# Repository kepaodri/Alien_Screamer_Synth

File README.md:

# Alien_Screamer_Synth
PCB design for "Alien Screamer" (modified) synthesizer (original design by Ray Wilson) in 4-layer stackup using THT components.

## 👽👾 Project Description
The **Alien Screamer** Analog Noise Box is a classic Lo-Fi analog synthesizer designed by Ray Wilson of *Music From Outer Space* capable to creating Sci-Fi sound effects. It serves as an excellent introductory project for synth-DIY enthusiasts, providing a hands-on way to learn about oscillators, modulation, and integrated circuit amplification.

For more detailed technical information and the original schematics, visit the [MFOS Alien Screamer Noise Box](https://musicfromouterspace.com/analogsynth_new/ALIENSCREAMER/ALIENSCREAMER.php)

## 🚀 Main Features
* **Wide-Range VCO:** A ramp-core oscillator driven by an exponential V-to-I converter, capable of frequencies from sub-audio clicks to 10kHz.
* **Integrated LFO:** A square-wave oscillator with adjustable rate and depth.
* **Waveform Shaping:** Toggle between square, low-pass filtered, and differentiated "tweet" waveforms for diverse modulation.
* **Sync Effects:** Hard-sync capability where the LFO resets the VCO for aggressive, complex timbres.
* **Built-in Audio:** Includes an LM386-based 1W amplifier and 8-Ohm speaker for portability.
* **9V-Battery Powered:** Optimized for low current draw (~10mA) on a single 9V battery.

## 🛠 Technical Overview
The circuit is built around 2x primary ICs:
- LM324 (Quad Op-Amp): Handles the VCO exponential converter, the ramp generator/comparator, and the LFO
- LM386 (Power Amp): Drives the internal speaker
- 4x Control Potentiometers: LFO Frequency + LFO Modulation Depth + VCO Frecuency + Volume 
- 2x Control Switches: LFO Modulation Waveform Selector + Synchro Effect

## 📂 Project Structure
* `doc/` - KiCad schematic and Datasheets.
* `bom/` - Bill of Materials (BOM) for component sourcing.
* `hardware/` - KiCad Design files (schematic and PCB layout routing).
* `gerbers/` - PCB gerber and drill files for production.
* `renders/` - High quality PCB images.

### PCB Features
- Layers: 4
- Thickness: 1.6mm
- Width: 250mm
- Heigth: 119.5mm

### 3D Render

## Tools Used
KiCad: 9.0.4

> **Note:** This project is designed for educational and DIY purposes. Original design by Ray Wilson (Music From Outer Space).

## Disclaimer
\*\*This design is provided "AS-IS" without any express or implied warranties.\*\* The author is not responsible for any damage to equipment, fire, or personal injury resulting from the assembly or use of this PCB.

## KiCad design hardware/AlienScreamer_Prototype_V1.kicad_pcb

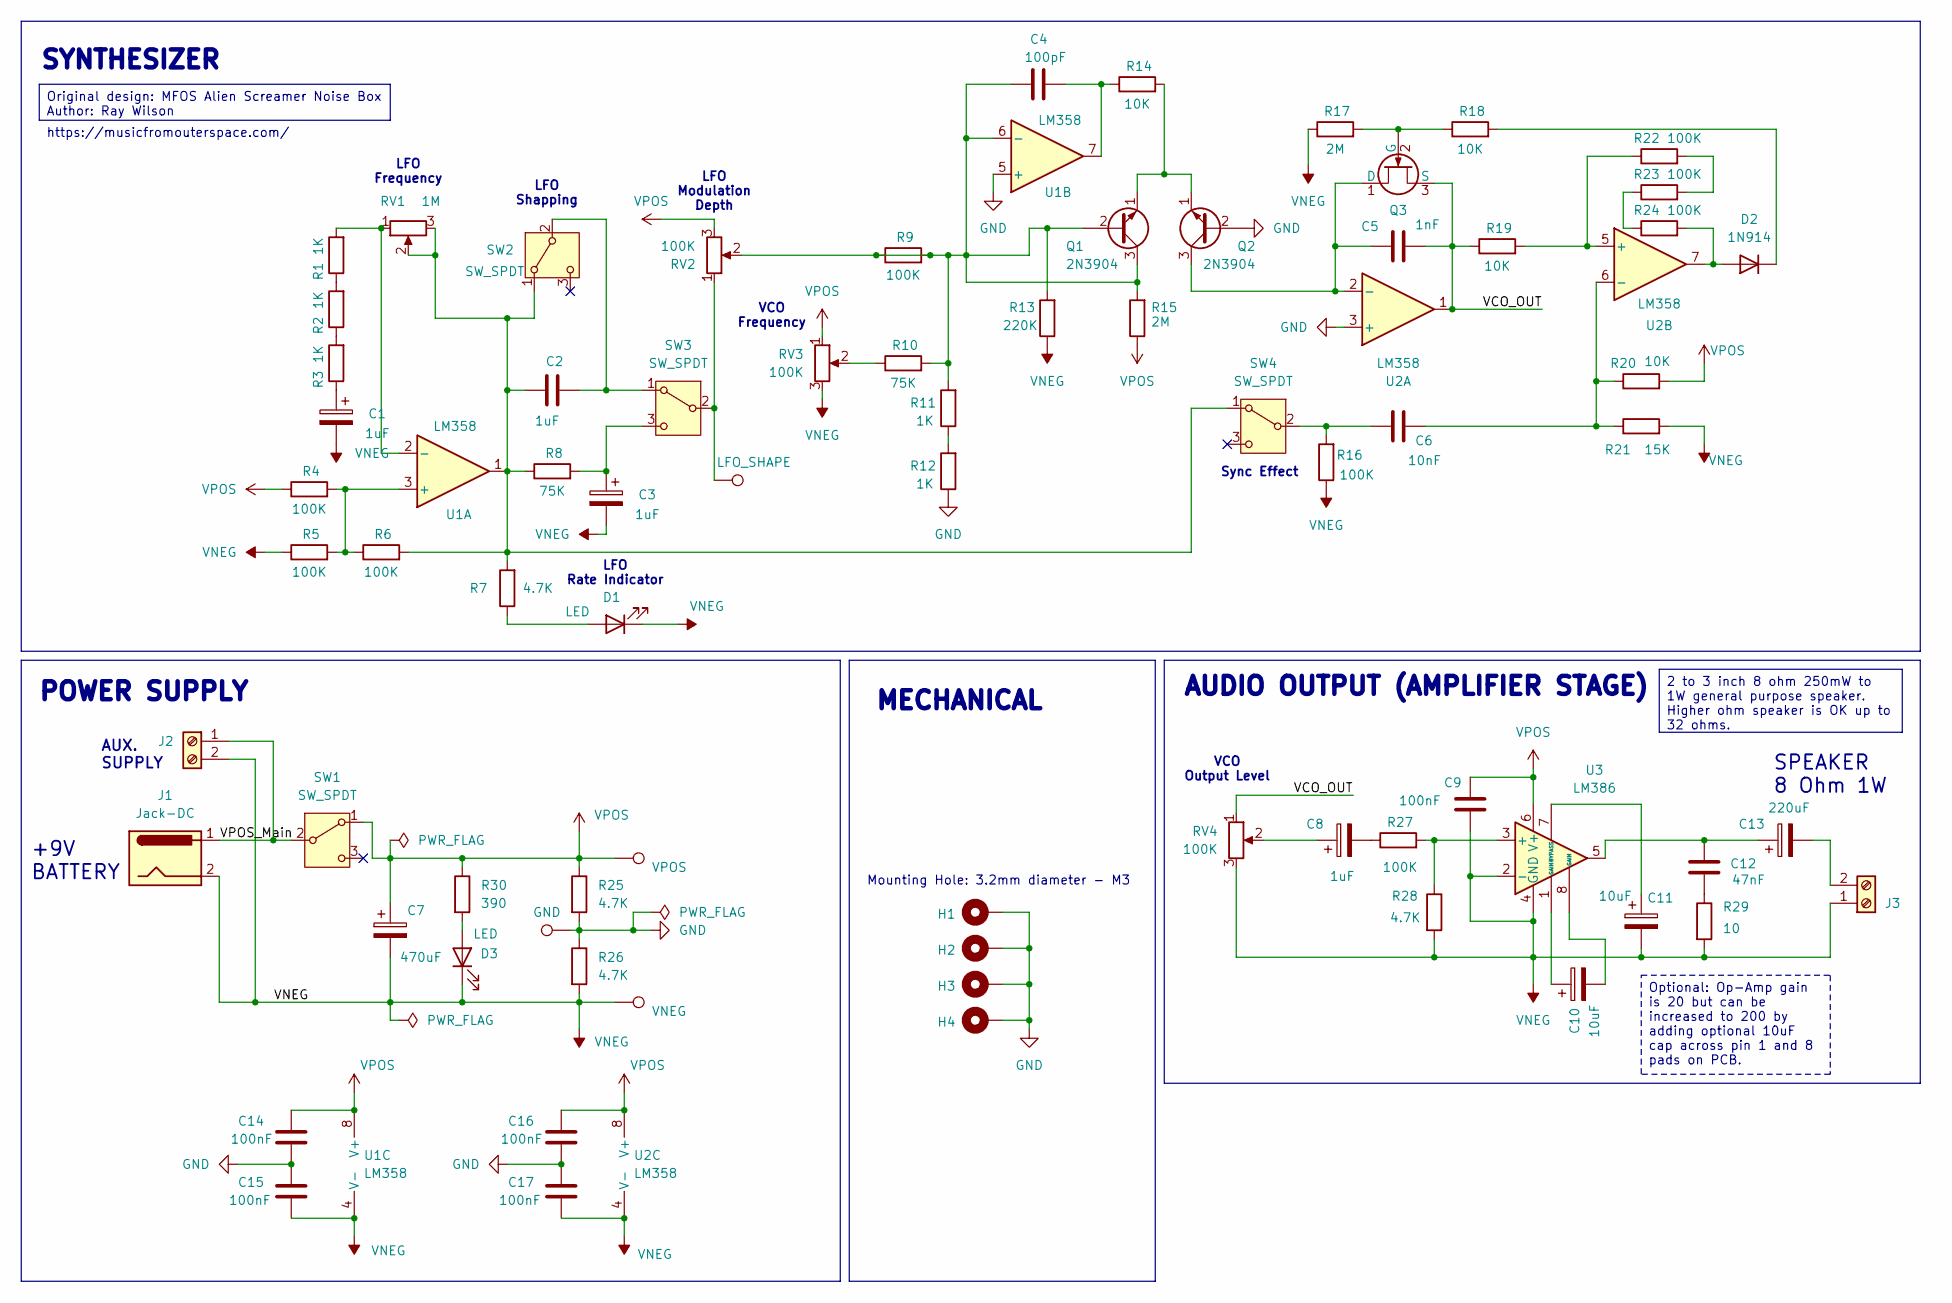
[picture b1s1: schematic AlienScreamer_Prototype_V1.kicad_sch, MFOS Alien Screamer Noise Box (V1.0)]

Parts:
C1, C3: 1uF; CP_Radial_D5.0mm_P2.00mm
C2, C8: 1uF; C_Rect_L13.0mm_W5.0mm_P10.00mm_FKS3_FKP3_MKS4
C4: 100pF; C_Disc_D4.7mm_W2.5mm_P5.00mm
C5: 1nF; C_Rect_L7.2mm_W2.5mm_P5.00mm_FKS2_FKP2_MKS2_MKP2
C6: 10nF; C_Rect_L7.2mm_W2.5mm_P5.00mm_FKS2_FKP2_MKS2_MKP2
C7: 470uF; CP_Radial_D10.0mm_P5.00mm
C9, C14, C15, C16, C17: 100nF; C_Rect_L7.2mm_W2.5mm_P5.00mm_FKS2_FKP2_MKS2_MKP2
C10, C11: 10uF; C_Disc_D7.5mm_W4.4mm_P5.00mm
C12: 47nF; C_Rect_L7.0mm_W2.5mm_P5.00mm
C13: 220uF; CP_Radial_D8.0mm_P3.50mm
D1, D3: LED; LED_D5.0mm
D2: 1N914; D_DO-35_SOD27_P7.62mm_Horizontal
GND1: GND; TestPoint_THTPad_D3.0mm_Drill1.5mm
H1, H2, H3, H4: MountingHole_Pad; MountingHole_3.2mm_M3_ISO14580_Pad_TopBottom
J1: Jack-DC; BarrelJack_Horizontal
J2, J3: Screw_Terminal_01x02; TerminalBlock_Phoenix_MPT-0,5-2-2.54_1x02_P2.54mm_Horizontal
LFO1: LFO_SHAPE; TestPoint_THTPad_D3.0mm_Drill1.5mm
Q1, Q2: 2N3904; TO-92_Inline
Q3: Q_NJFET_DGS; TO-92_Inline
R1, R2, R3, R11, R12: 1K; R_Axial_DIN0207_L6.3mm_D2.5mm_P7.62mm_Horizontal
R4, R5, R6, R9, R16, R22, R23, R24, R27: 100K; R_Axial_DIN0207_L6.3mm_D2.5mm_P7.62mm_Horizontal
R7, R25, R26, R28: 4.7K; R_Axial_DIN0207_L6.3mm_D2.5mm_P7.62mm_Horizontal
R8, R10: 75K; R_Axial_DIN0207_L6.3mm_D2.5mm_P7.62mm_Horizontal
R13: 220K; R_Axial_DIN0207_L6.3mm_D2.5mm_P7.62mm_Horizontal
R14, R18, R19, R20: 10K; R_Axial_DIN0207_L6.3mm_D2.5mm_P7.62mm_Horizontal
R15, R17: 2M; R_Axial_DIN0207_L6.3mm_D2.5mm_P7.62mm_Horizontal
R21: 15K; R_Axial_DIN0207_L6.3mm_D2.5mm_P7.62mm_Horizontal
R29: 10; R_Axial_DIN0207_L6.3mm_D2.5mm_P7.62mm_Horizontal
R30: 390; R_Axial_DIN0207_L6.3mm_D2.5mm_P7.62mm_Horizontal
RV1: 1M; Potentiometer_Bourns_PTV09A-1_Single_Vertical
RV2, RV3, RV4: 100K; Potentiometer_Bourns_PTV09A-1_Single_Vertical
SW1, SW2, SW3, SW4: SW_SPDT; SW_Slide-03_Wuerth-WS-SLTV_10x2.5x6.4_P2.54mm
U1, U2: LM358; DIP-8_W7.62mm_Socket_LongPads
U3: LM386; DIP-8_W7.62mm_Socket_LongPads
VNEG1: VNEG; TestPoint_THTPad_D3.0mm_Drill1.5mm
VPOS1: VPOS; TestPoint_THTPad_D3.0mm_Drill1.5mm

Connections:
/VCO_OUT: C5.1, Q3.3 (S), R19.1, RV4.1, U2.1
/VPOS_Main: J1.1, J2.1, SW1.2 (B)
GND: C14.2, C15.1, C16.2, C17.1, GND1.1, H1.1, H2.1, H3.1, H4.1, Q2.2 (B), R12.1, R25.2, R26.1, U1.5 (+), U2.3 (+)
unnamed: C1.1, R3.1
unnamed: C4.1, R14.1, U1.7
unnamed: C8.1, RV4.2
unnamed: C8.2, R27.1
unnamed: C10.1, U3.1 (GAIN)
unnamed: C10.2, U3.8 (GAIN)
unnamed: C12.1, C13.1, U3.5
unnamed: C12.2, R29.1
unnamed: D1.2 (A), R7.1
unnamed: D2.2 (A), R24.2, U2.7
unnamed: D2.1 (K), R18.2
unnamed: D3.2 (A), R30.2
unnamed: C13.2, J3.2
unnamed: Q1.1 (E), Q2.1 (E), R14.2
unnamed: C5.2, Q2.3 (C), Q3.1 (D), U2.2 (-)
unnamed: Q3.2 (G), R17.2, R18.1
unnamed: R1.1, R2.2
unnamed: R2.1, R3.2
unnamed: R10.1, RV3.2
unnamed: R11.1, R12.2
unnamed: R22.2, R23.2
unnamed: R23.1, R24.1
unnamed: C2.2, R6.2, R7.2, R8.1, RV1.2, RV1.3, SW2.1 (A), SW4.1 (A), U1.1
unnamed: C2.1, SW2.2 (B), SW3.1 (A)
unnamed: LFO1.1, RV2.1, SW3.2 (B)
unnamed: C3.1, R8.2, SW3.3 (C)
unnamed: C6.2, R16.2, SW4.2 (B)
unnamed: R4.2, R5.2, R6.1, U1.3 (+)
unnamed: R1.2, RV1.1, U1.2 (-)
unnamed: R19.2, R22.1, U2.5 (+)
unnamed: C6.1, R20.1, R21.1, U2.6 (-)
unnamed: R27.2, R28.1, U3.3 (+)
unnamed: C11.1, U3.7 (BYPASS)
VNEG: C1.2, C3.2, C7.2, C9.2, C11.2, C15.2, C17.2, D1.1 (K), D3.1 (K), J1.2, J2.2, J3.1, R5.1, R13.1, R16.1, R17.1, R21.2, R26.2, R28.2, R29.2, RV3.3, RV4.3, U1.4 (V-), U2.4 (V-), U3.2 (-), U3.4 (GND), VNEG1.1
VPOS: C7.1, C9.1, C14.1, C16.1, R4.1, R15.1, R20.2, R25.1, R30.1, RV2.3, RV3.1, SW1.1 (A), U1.8 (V+), U2.8 (V+), U3.6 (V+), VPOS1.1

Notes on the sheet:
LFO Modulation Depth
SPEAKER 8 Ohm 1W
AUDIO OUTPUT (AMPLIFIER STAGE)
+9V BATTERY
Mounting Hole: 3.2mm diameter - M3
LFO Frequency
LFO Shapping
SYNTHESIZER
MECHANICAL
VCO Frequency
VCO Output Level
AUX. SUPPLY
POWER SUPPLY
Sync Effect
LFO Rate Indicator
Original design: MFOS Alien Screamer Noise Box Author: Ray Wilson
Optional: Op-Amp gain is 20 but can be increased to 200 by adding optional 10uF cap across pin 1 and 8 pads on PCB.
https://musicfromouterspace.com/
2 to 3 inch 8 ohm 250mW to 1W general purpose speaker. Higher ohm speaker is OK up to 32 ohms.

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
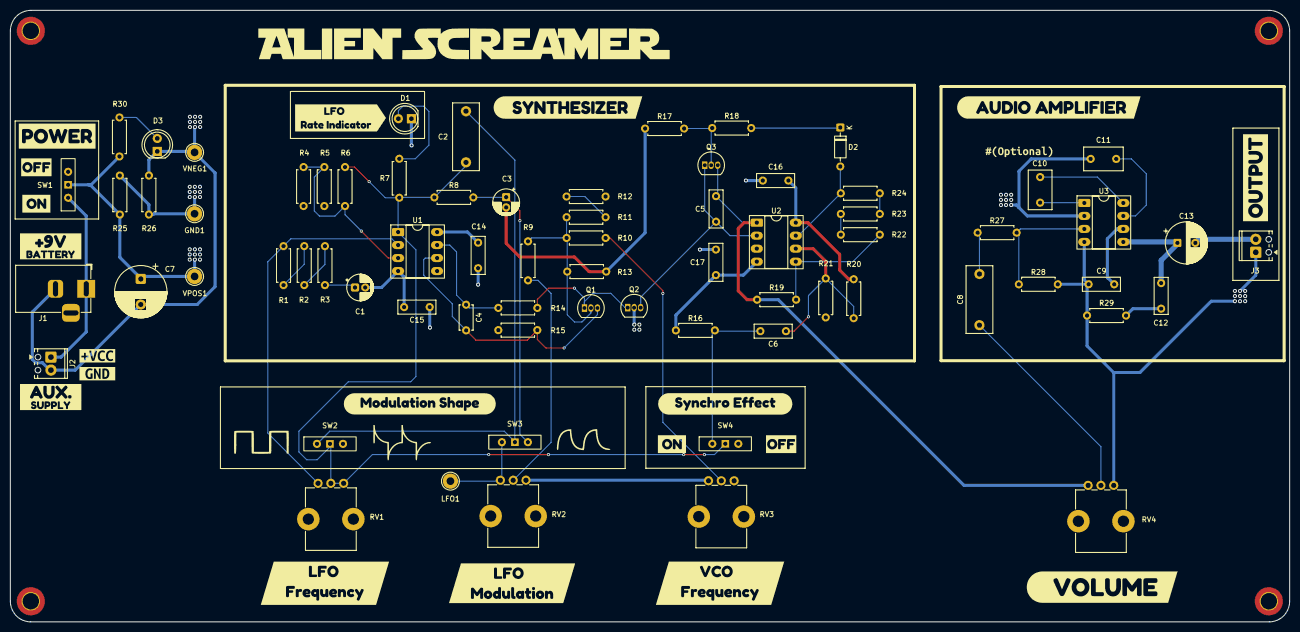
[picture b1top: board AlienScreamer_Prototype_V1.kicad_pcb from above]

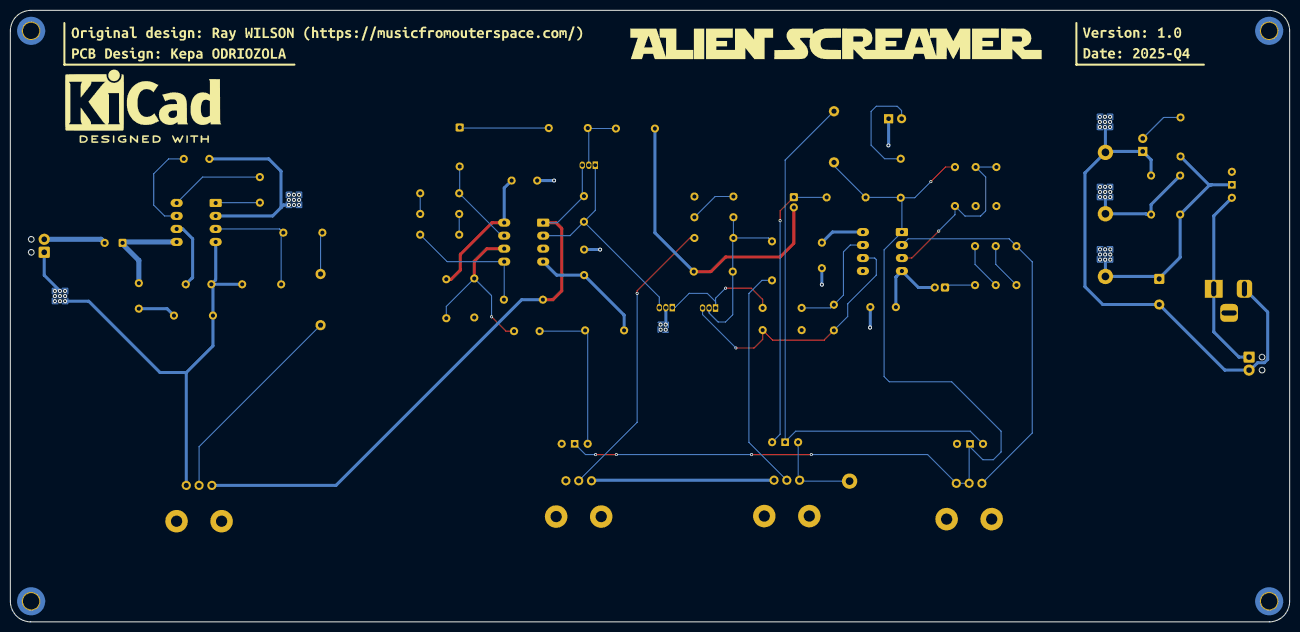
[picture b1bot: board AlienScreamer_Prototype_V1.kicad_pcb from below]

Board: 4 copper layers, 250.0 x 119.5 mm, 99 parts (2 on the bottom side), 41 nets.

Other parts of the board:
kibuzzard-68CDBF79: G***; kibuzzard-68CDBF79
kibuzzard-68CDBFF1: G***; kibuzzard-68CDBFF1
kibuzzard-68FBF4C5: G***; kibuzzard-68FBF4C5
kibuzzard-69028D19: G***; kibuzzard-69028D19
kibuzzard-69028F34, kibuzzard-69028F34#2: G***; kibuzzard-69028F34
kibuzzard-69028F53: G***; kibuzzard-69028F53
kibuzzard-69028FA7: G***; kibuzzard-69028FA7
kibuzzard-69029B16: G***; kibuzzard-69029B16
kibuzzard-69029C04: G***; kibuzzard-69029C04
kibuzzard-69029C48: G***; kibuzzard-69029C48
kibuzzard-690285FB: G***; kibuzzard-690285FB
kibuzzard-690296C8: G***; kibuzzard-690296C8
kibuzzard-690296DD: G***; kibuzzard-690296DD
kibuzzard-690299FD: G***; kibuzzard-690299FD
kibuzzard-690449BB: G***; kibuzzard-690449BB
kibuzzard-690449D3: G***; kibuzzard-690449D3
kibuzzard-6902900C: G***; kibuzzard-6902900C
kibuzzard-6902970A: G***; kibuzzard-6902970A
kibuzzard-69028614: G***; kibuzzard-69028614
kibuzzard-69028628: G***; kibuzzard-69028628
kibuzzard-69028715: G***; kibuzzard-69028715
kibuzzard-69029716: G***; kibuzzard-69029716
kibuzzard-69029751: G***; kibuzzard-69029751
